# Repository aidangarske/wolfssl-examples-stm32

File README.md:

# wolfSSL Examples for STM32

* [STM32H743_Nucleo_ETH](STM32H743_Nucleo_ETH): wolfSSL TLS with TPM example
* [STM32F446ZE_Nucleo_PQ](STM32F446ZE_Nucleo_PQ): wolfSSL Post-Quantum example, this is a pointer to another repository
* [STM32MP135F-DK](STM32MP135F-DK): wolfSSL echoclient example using FreeRTOS and LwIP
* [wolfDemo](wolfDemo): A demonstration board designed around an STM32U585 with multiple examples

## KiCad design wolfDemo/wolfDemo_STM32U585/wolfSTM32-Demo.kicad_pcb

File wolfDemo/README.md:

# wolfDemo

The wolfDemo project is an example board intended to be used for demonstrations
of wolfSSL software projects on wolfSSL branded hardware.

It is intended to be easy to pick up and use, with a USB UART chip to program
the board and get logging information. It also has two open standard mikroBus
sockets to expand with thousands of different peripherals.

The following subdirectories exist here:

## [wolfDemo_STM32U585](wolfDemo_STM32U585)

The wolfDemo board KiCad project files.

The board is intended to be manufactured using white PCBs, there is an area on
the rear for JLCPCB QR codes. It is recommended that lead-free HASL is used.

There is also the following associated files:

### [wolfDemo v1 Manual.pdf](<wolfDemo v1 Manual.pdf>)

This is an export of the user manual for the board.

### [wolfDemo_backboard.stl](wolfDemo_backboard.stl)

This is an STL to 3D print the backboard for the wolfDemo board.

It should be printed in white, using supports for the hex holes at the bottom.

The boards are bolted together using M3 7mm bolts and M3 nuts. Five 12.7mm
rubber feet are stuck onto this board to stop it slipping on surfaces it rests
on.

## [wolfDemo_ST33](wolfDemo_ST33)

This is a mikroBus click board design for the ST33K TPM chip.

Documentation for this is coming soon.

## [examples](examples)

All the code examples for the wolfDemo board can be found here.

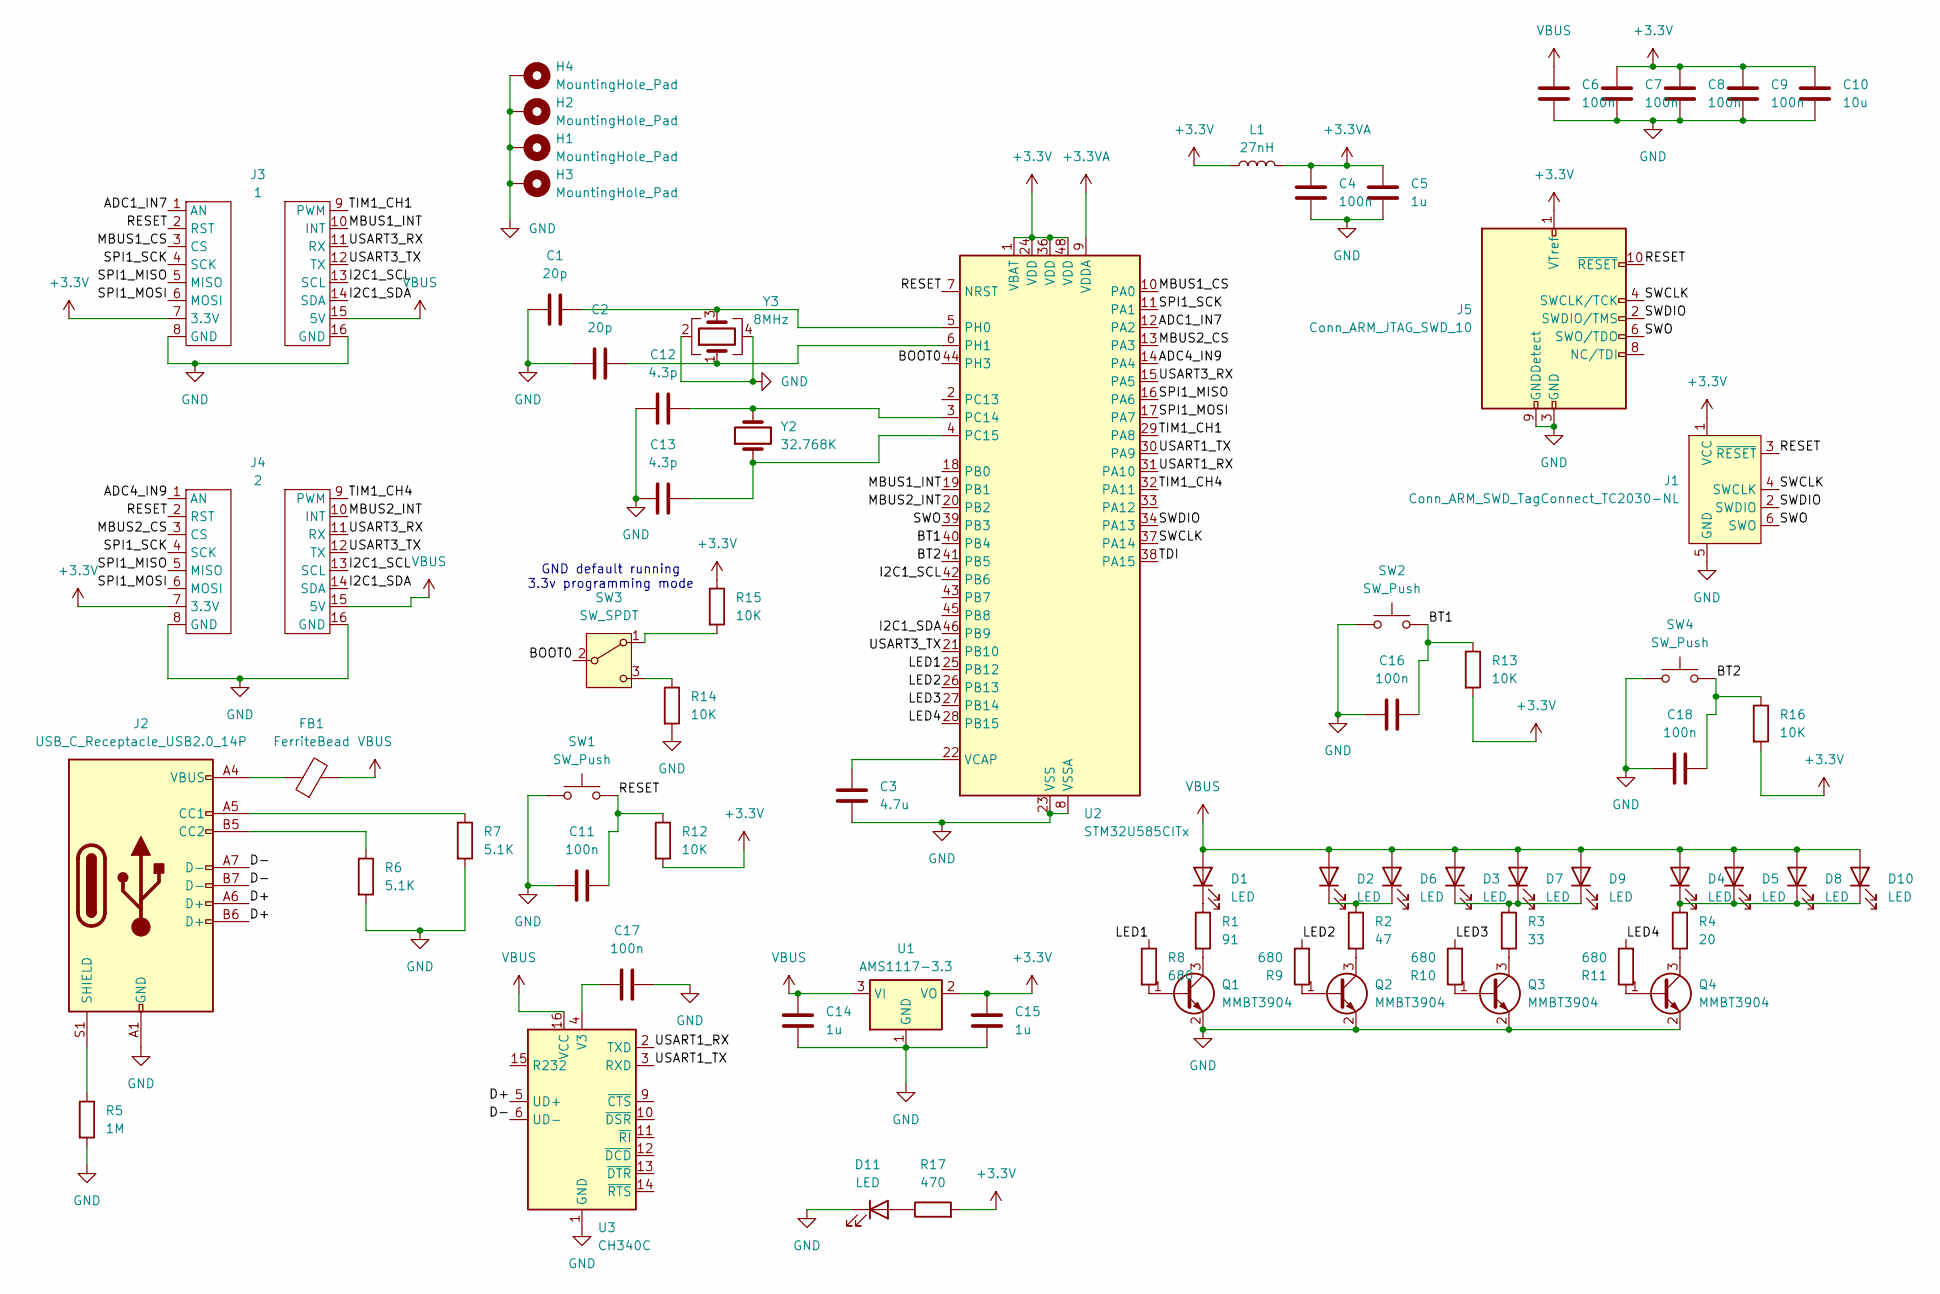
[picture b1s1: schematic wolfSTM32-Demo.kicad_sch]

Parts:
C1, C2: 20p; C_0603_1608Metric_Pad1.08x0.95mm_HandSolder; LCSC C1648
C3: 4.7u; C_0805_2012Metric_Pad1.18x1.45mm_HandSolder; LCSC C1779
C4, C6, C7, C8, C9, C11, C16, C17, C18: 100n; C_0603_1608Metric_Pad1.08x0.95mm_HandSolder; LCSC C14663
C5, C14, C15: 1u; C_0805_2012Metric_Pad1.18x1.45mm_HandSolder; LCSC C28323
C10: 10u; C_0805_2012Metric_Pad1.18x1.45mm_HandSolder; LCSC C15850
C12, C13: 4.3p; C_0603_1608Metric_Pad1.08x0.95mm_HandSolder; LCSC C376790
D1, D2, D3, D4, D5, D6, D7, D8, D9, D10: LED; SunLED
D11: LED; LED_0603_1608Metric_Pad1.05x0.95mm_HandSolder; LCSC C72041
FB1: FerriteBead; L_0805_2012Metric_Pad1.05x1.20mm_HandSolder; LCSC C1017
H1, H2, H3, H4: MountingHole_Pad; MountingHole_3.2mm_M3_Pad_Via
J1: Conn_ARM_SWD_TagConnect_TC2030-NL; Tag-Connect_TC2030-IDC-NL_2x03_P1.27mm_Vertical
J2: USB_C_Receptacle_USB2.0_14P; USB_C_Receptacle_GCT_USB4085; LCSC C36936564
J3: 1; MIKROBUS_HOST_CONN
J4: 2; MIKROBUS_HOST_CONN
J5: Conn_ARM_JTAG_SWD_10; IDC-Header_2x05_P2.54mm_Vertical
L1: 27nH; L_0603_1608Metric_Pad1.05x0.95mm_HandSolder; LCSC C90208
Q1, Q2, Q3, Q4: MMBT3904; SOT-23; LCSC C20526
R1: 91; R_0603_1608Metric_Pad0.98x0.95mm_HandSolder; LCSC C25199
R2: 47; R_0603_1608Metric_Pad0.98x0.95mm_HandSolder; LCSC C23182
R3: 33; R_0603_1608Metric_Pad0.98x0.95mm_HandSolder; LCSC C23140
R4: 20; R_0603_1608Metric_Pad0.98x0.95mm_HandSolder; LCSC C22950
R5: 1M; R_0603_1608Metric_Pad0.98x0.95mm_HandSolder; LCSC C22935
R6, R7: 5.1K; R_0603_1608Metric_Pad0.98x0.95mm_HandSolder; LCSC C23186
R8, R9, R10, R11: 680; R_0603_1608Metric_Pad0.98x0.95mm_HandSolder; LCSC C23228
R12, R13, R14, R15, R16: 10K; R_0603_1608Metric_Pad0.98x0.95mm_HandSolder; LCSC C25804
R17: 470; R_0603_1608Metric_Pad0.98x0.95mm_HandSolder; LCSC C23179
SW1, SW2, SW4: SW_Push; SW_SPST_EVQP2_ShortPushTravel_H2.1mm; LCSC C79161
SW3: SW_SPDT; SW_SPDT_PCM12; LCSC C109335
U1: AMS1117-3.3; SOT-223-3_TabPin2; LCSC C277892
U2: STM32U585CITx; LQFP-48_7x7mm_P0.5mm
U3: CH340C; SOIC-16_3.9x9.9mm_P1.27mm; LCSC C84681
Y2: 32.768K; Crystal_SMD_3215-2Pin_3.2x1.5mm; LCSC C95361
Y3: 8MHz; Crystal_SMD_3225-4Pin_3.2x2.5mm; LCSC C2682775

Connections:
+3.3V: C7.1, C8.1, C9.1, C10.1, C15.1, J1.1 (VCC), J3.7 (3.3V), J4.7 (3.3V), J5.1 (VTref), L1.1, R12.2, R13.2, R15.1, R16.2, R17.2, U1.2 (VO), U2.1 (VBAT), U2.24 (VDD), U2.36 (VDD), U2.48 (VDD)
+3.3VA: C4.1, C5.1, L1.2, U2.9 (VDDA)
/ADC1_IN7: J3.1 (AN), U2.12 (PA2)
/ADC4_IN9: J4.1 (AN), U2.14 (PA4)
/BOOT0: SW3.2 (B), U2.44 (PH3)
/BT1: C16.2, R13.1, SW2.2, U2.40 (PB4)
/BT2: C18.2, R16.1, SW4.2, U2.41 (PB5)
/D+: J2.A6 (D+), J2.B6 (D+), U3.5 (UD+)
/D-: J2.A7 (D-), J2.B7 (D-), U3.6 (UD-)
/I2C1_SCL: J3.13 (SCL), J4.13 (SCL), U2.42 (PB6)
/I2C1_SDA: J3.14 (SDA), J4.14 (SDA), U2.46 (PB9)
/LED1: R8.1, U2.25 (PB12)
/LED2: R9.2, U2.26 (PB13)
/LED3: R10.2, U2.27 (PB14)
/LED4: R11.2, U2.28 (PB15)
/MBUS1_CS: J3.3 (CS), U2.10 (PA0)
/MBUS1_INT: J3.10 (INT), U2.19 (PB1)
/MBUS2_CS: J4.3 (CS), U2.13 (PA3)
/MBUS2_INT: J4.10 (INT), U2.20 (PB2)
/RESET: C11.2, J1.3 (~RESET), J3.2 (RST), J4.2 (RST), J5.10 (~RESET), R12.1, SW1.2, U2.7 (NRST)
/SPI1_MISO: J3.5 (MISO), J4.5 (MISO), U2.16 (PA6)
/SPI1_MOSI: J3.6 (MOSI), J4.6 (MOSI), U2.17 (PA7)
/SPI1_SCK: J3.4 (SCK), J4.4 (SCK), U2.11 (PA1)
/SWCLK: J1.4 (SWCLK), J5.4 (SWCLK/TCK), U2.37 (PA14)
/SWDIO: J1.2 (SWDIO), J5.2 (SWDIO/TMS), U2.34 (PA13)
/SWO: J1.6 (SWO), J5.6 (SWO/TDO), U2.39 (PB3)
/TDI: U2.38 (PA15)
/TIM1_CH1: J3.9 (PWM), U2.29 (PA8)
/TIM1_CH4: J4.9 (PWM), U2.32 (PA11)
/USART1_RX: U2.31 (PA10), U3.2 (TXD)
/USART1_TX: U2.30 (PA9), U3.3 (RXD)
/USART3_RX: J3.11 (RX), J4.11 (RX), U2.15 (PA5)
/USART3_TX: J3.12 (TX), J4.12 (TX), U2.21 (PB10)
GND: C1.1, C2.2, C3.2, C4.2, C5.2, C6.2, C7.2, C8.2, C9.2, C10.2, C11.1, C12.1, C13.1, C14.2, C15.2, C16.1, C17.2, C18.1, D11.1 (K), H1.1, H2.1, H3.1, H4.1, J1.5 (GND), J2.A1 (GND), J2.A12 (GND), J2.B1 (GND), J2.B12 (GND), J3.8 (GND), J3.16 (GND), J4.8 (GND), J4.16 (GND), J5.3 (GND), J5.5 (GND), J5.9 (GNDDetect), Q1.2 (E), Q2.2 (E), Q3.2 (E), Q4.2 (E), R5.2, R6.2, R7.2, R14.2, SW1.1, SW2.1, SW4.1, U1.1 (GND), U2.8 (VSSA), U2.23 (VSS), U2.35 (VSS), U2.47 (VSS), U3.1 (GND), Y3.2, Y3.4
unnamed: D1.1 (K), R1.1
unnamed: D2.1 (K), D6.1 (K), R2.1
unnamed: D3.1 (K), D7.1 (K), D9.1 (K), R3.1
unnamed: D4.1 (K), D5.1 (K), D8.1 (K), D10.1 (K), R4.1
unnamed: D11.2 (A), R17.1
unnamed: FB1.1, J2.A4 (VBUS), J2.A9 (VBUS), J2.B4 (VBUS), J2.B9 (VBUS)
unnamed: J2.A5 (CC1), R7.1
unnamed: J2.B5 (CC2), R6.1
unnamed: J2.S1 (SHIELD), R5.1
unnamed: Q1.1 (B), R8.2
unnamed: Q1.3 (C), R1.2
unnamed: Q2.1 (B), R9.1
unnamed: Q2.3 (C), R2.2
unnamed: Q3.1 (B), R10.1
unnamed: Q3.3 (C), R3.2
unnamed: Q4.1 (B), R11.1
unnamed: Q4.3 (C), R4.2
unnamed: R15.2, SW3.1 (A)
unnamed: R14.1, SW3.3 (C)
unnamed: C12.2, U2.3 (PC14), Y2.2
unnamed: C13.2, U2.4 (PC15), Y2.1
unnamed: C1.2, U2.5 (PH0), Y3.3
unnamed: C2.1, U2.6 (PH1), Y3.1
unnamed: C3.1, U2.22 (VCAP)
unnamed: C17.1, U3.4 (V3)
VBUS: C6.1, C14.1, D1.2 (A), D2.2 (A), D3.2 (A), D4.2 (A), D5.2 (A), D6.2 (A), D7.2 (A), D8.2 (A), D9.2 (A), D10.2 (A), FB1.2, J3.15 (5V), J4.15 (5V), U1.3 (VI), U3.16 (VCC)

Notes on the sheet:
GND default running 3.3v programming mode

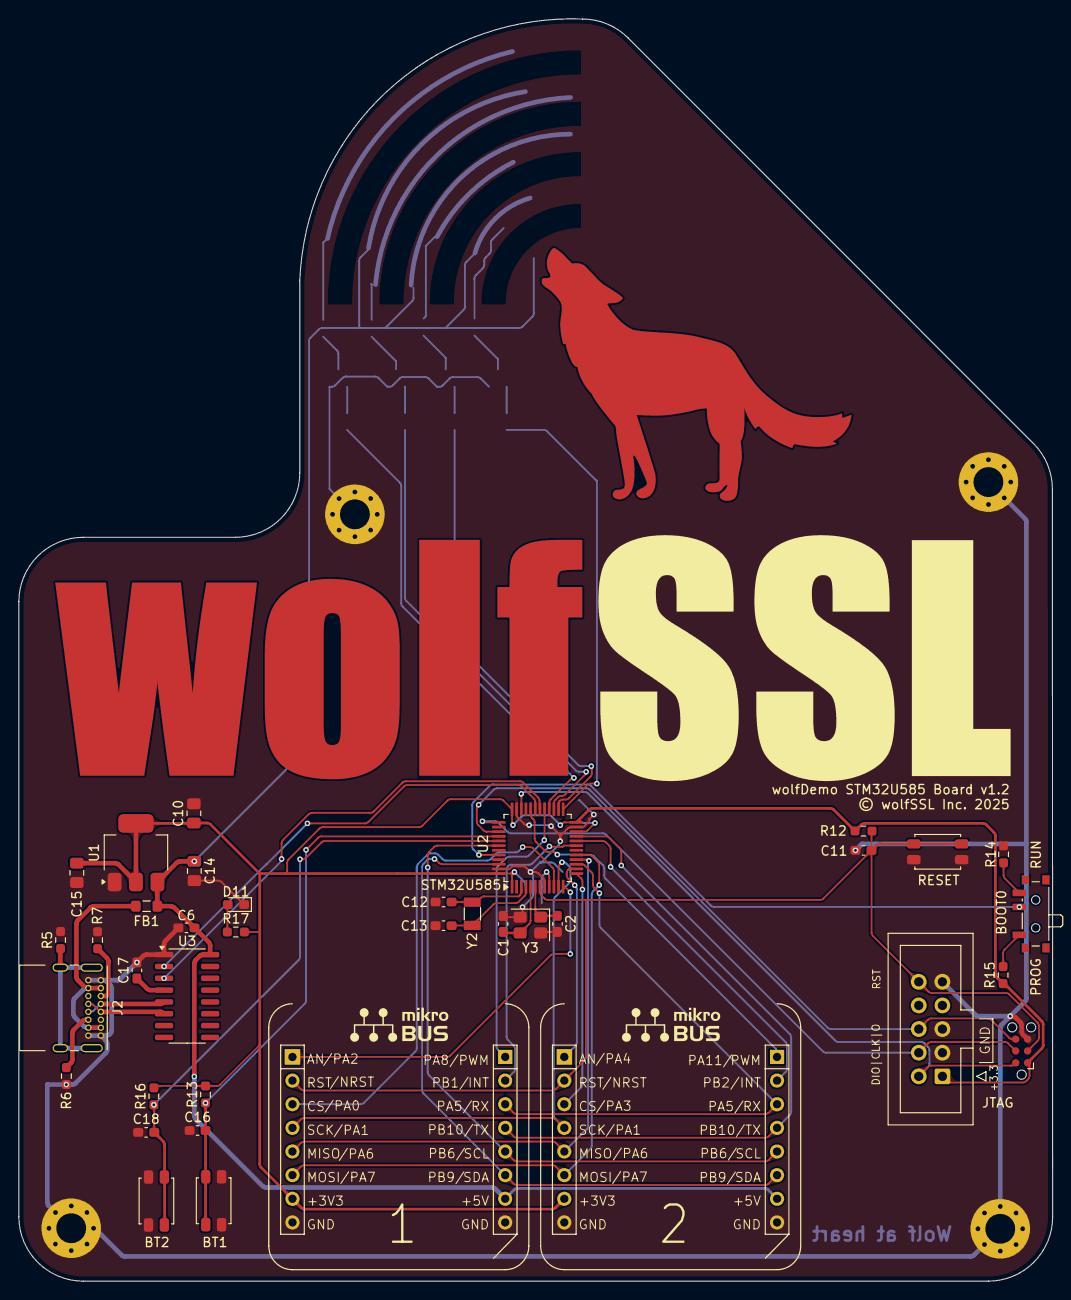
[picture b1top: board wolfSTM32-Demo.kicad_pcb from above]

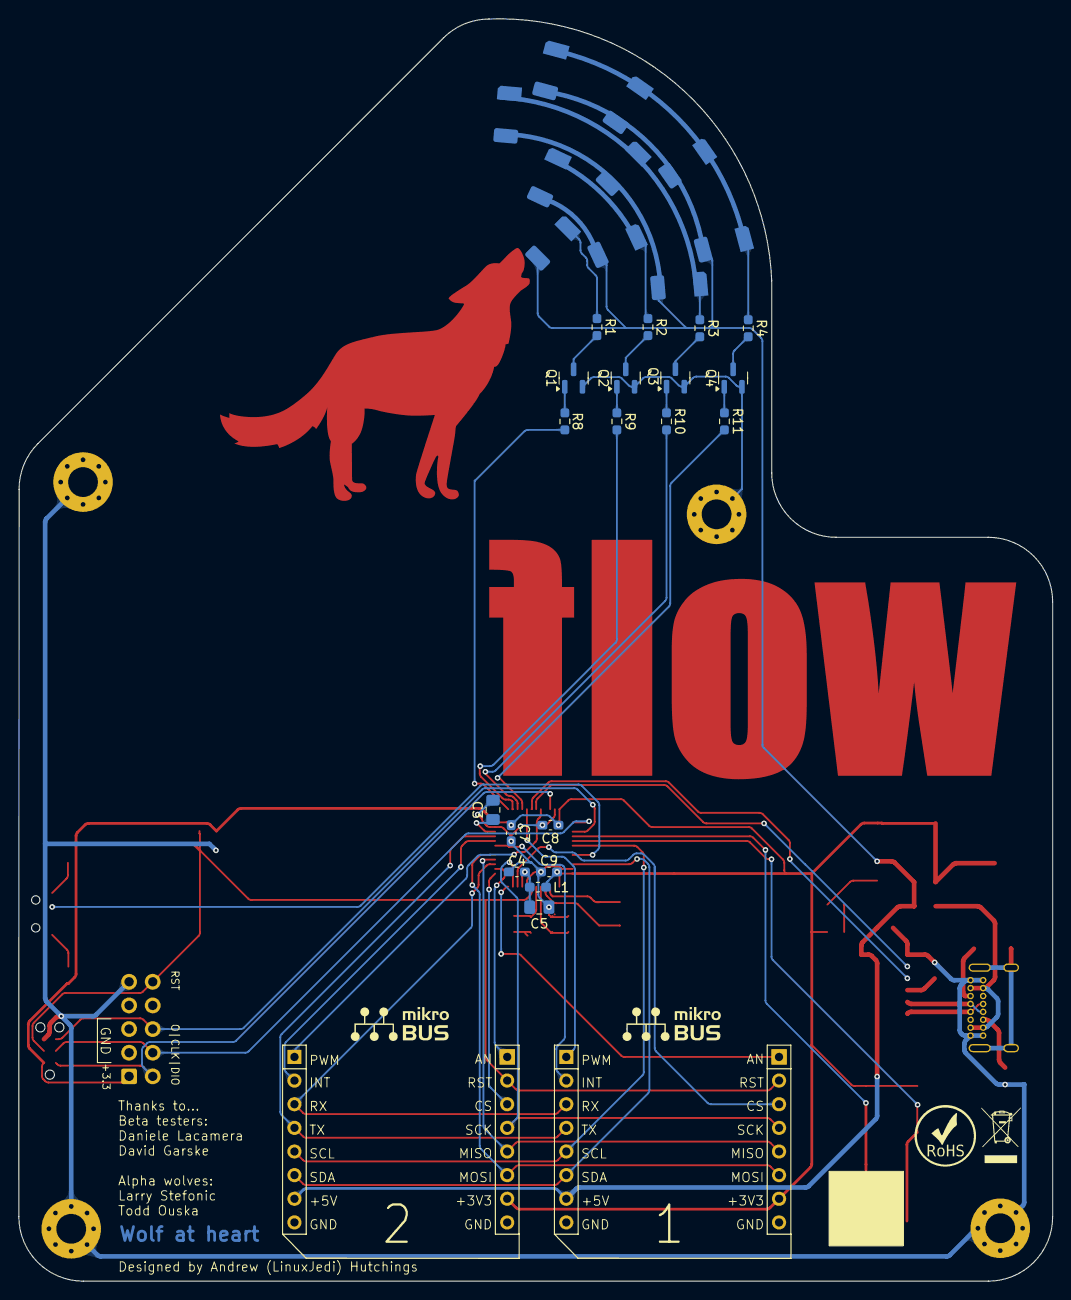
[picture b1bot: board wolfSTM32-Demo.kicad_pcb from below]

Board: 2 copper layers, 111.1 x 135.6 mm, 70 parts (29 on the bottom side), 59 nets.

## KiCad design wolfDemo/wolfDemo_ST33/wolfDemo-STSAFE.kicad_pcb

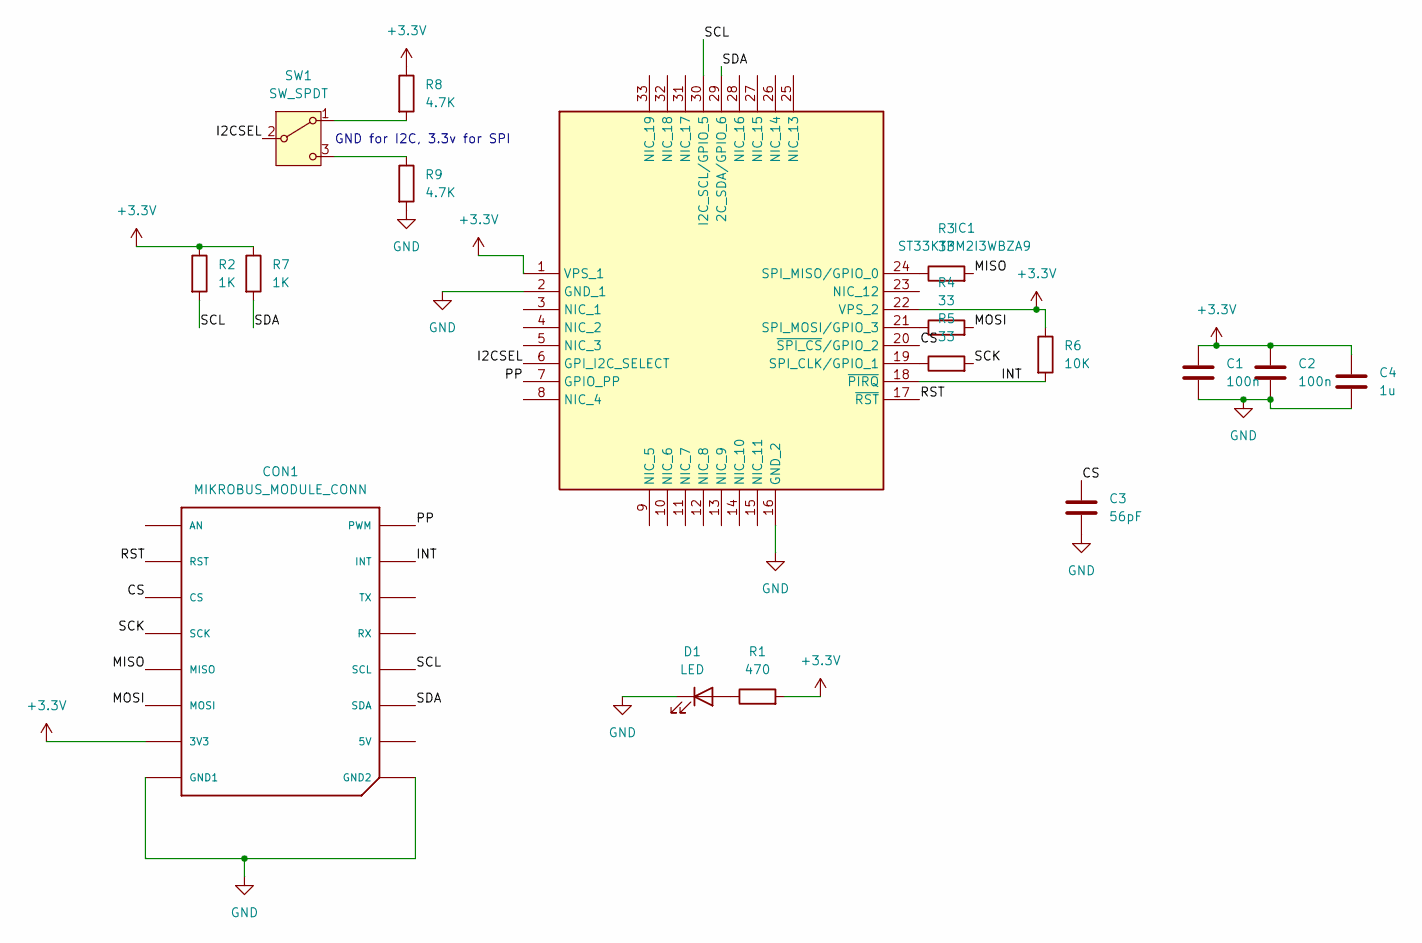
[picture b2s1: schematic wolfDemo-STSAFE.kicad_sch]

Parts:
C1, C2: 100n; C_0603_1608Metric_Pad1.08x0.95mm_HandSolder
C3: 56pF; C_0603_1608Metric_Pad1.08x0.95mm_HandSolder
C4: 1u; C_0805_2012Metric_Pad1.18x1.45mm_HandSolder
CON1: MIKROBUS_MODULE_CONN
D1: LED; LED_0603_1608Metric_Pad1.05x0.95mm_HandSolder; LCSC C72041
IC1: ST33KTPM2I3WBZA9; QFN50P500X500X65-33N-D; Manufacturer_Part_Number ST33KTPM2I3WBZA9; Mouser Part Number 511-ST33KTPM2I3WBZA9
R1: 470; R_0603_1608Metric_Pad0.98x0.95mm_HandSolder; LCSC C23179
R2, R7: 1K; R_0603_1608Metric_Pad0.98x0.95mm_HandSolder
R3, R4, R5: 33; R_0603_1608Metric_Pad0.98x0.95mm_HandSolder
R6: 10K; R_0603_1608Metric_Pad0.98x0.95mm_HandSolder
R8, R9: 4.7K; R_0603_1608Metric_Pad0.98x0.95mm_HandSolder
SW1: SW_SPDT; SW_SPDT_PCM12; LCSC C109335

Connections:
+3.3V: C1.1, C2.1, C4.1, CON1.P7 (3V3), IC1.1 (VPS_1), IC1.22 (VPS_2), R1.2, R2.1, R6.1, R7.1, R8.1
/CS: C3.1, CON1.P3 (CS), IC1.20 (~SPI_CS/GPIO_2)
/I2CSEL: IC1.6 (GPI_I2C_SELECT), SW1.2 (B)
/INT: CON1.P15 (INT), IC1.18 (~PIRQ), R6.2
/MISO: CON1.P5 (MISO), R3.2
/MOSI: CON1.P6 (MOSI), R4.2
/PP: CON1.P16 (PWM), IC1.7 (GPIO_PP)
/RST: CON1.P2 (RST), IC1.17 (~RST)
/SCK: CON1.P4 (SCK), R5.2
/SCL: CON1.P12 (SCL), IC1.30 (I2C_SCL/GPIO_5), R2.2
/SDA: CON1.P11 (SDA), IC1.29 (2C_SDA/GPIO_6), R7.2
GND: C1.2, C2.2, C3.2, C4.2, CON1.P8 (GND1), CON1.P9 (GND2), D1.1 (K), IC1.2 (GND_1), IC1.16 (GND_2), R9.2
unnamed: D1.2 (A), R1.1
unnamed: IC1.19 (SPI_CLK/GPIO_1), R5.1
unnamed: IC1.24 (SPI_MISO/GPIO_0), R3.1
unnamed: IC1.21 (SPI_MOSI/GPIO_3), R4.1
unnamed: R8.2, SW1.1 (A)
unnamed: R9.1, SW1.3 (C)

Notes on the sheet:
GND for I2C, 3.3v for SPI

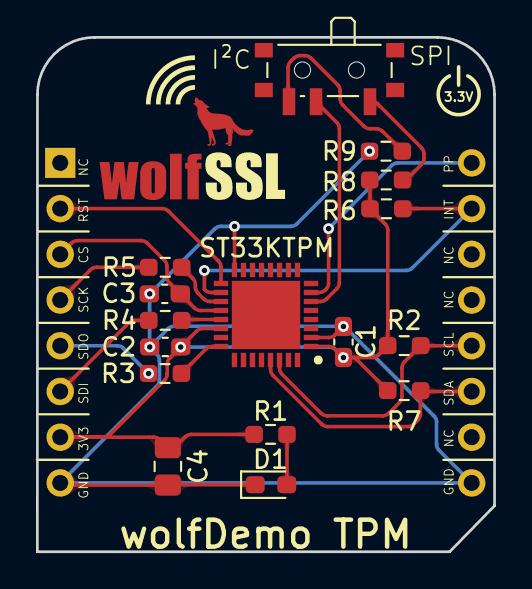
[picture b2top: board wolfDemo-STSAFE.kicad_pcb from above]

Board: 2 copper layers, 25.4 x 28.6 mm, 17 parts (0 on the bottom side), 18 nets.

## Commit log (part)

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2026-02-07 Add NUCLEO-H563ZI wolfIP example
    Self-contained example with wolfIP Cube Pack included.
    Demonstrates ICMP (ping) using bare-metal Ethernet driver.
2026-02-13 Add NUCLEO-H563ZI wolfIP CubeMX example
    - Add NUCLEO-H563ZI/.ioc pre-configured CubeMX project
    - ETH RMII mode with correct GPIO pins
    - NVIC ETH interrupt enabled
    - wolfIP Core and Eth components enabled
    - Update README with pin configuration notes
    - Clarify GPIO pin requirements for custom boards
2026-04-28 STM32F437_EVAL_Test: wolfCrypt test and benchmark for STM32F437 (STM32439I-EVAL)
    Bare-metal wolfCrypt self-test and benchmark for the STM32439I-EVAL
    (G-EVAL) board with STM32F437IIHx. Two build variants:
    make CONFIG=c test # Pure C SP math (sp_c32.c)
    make CONFIG=hw test # STM32 HW CRYP + HASH offload
    Features:
    - ECC P-256/384/521, Curve25519, Ed25519 (SP math C)
2026-05-06 Add STM32U385RG_Nucleo_MQTT demo
    NUCLEO-U385RG-Q bare-metal demo: wolfCrypt test/bench, wolfMQTT TLS 1.3
    mTLS over UART (P-384 ECDSA, AES-128-GCM-SHA256), FIPS 140-3 Ready,
    and wolfBoot signed-boot integration. Four CONFIG variants
    (c / asm / hw / fips). HW HASH + HW AES via STM32U3 HAL_HASH/HAL_CRYP
    once the wolfSSL upstream WOLFSSL_STM32U3 macro is available.
    Verified end-to-end on hardware: wolfcrypt_test PASS for all variants,
2026-05-07 Use download path for cube pack

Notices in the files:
wolfDemo/wolfDemo_STM32U585/wolfSTM32-Demo.kicad_pcb:
© wolfSSL Inc. 2025
